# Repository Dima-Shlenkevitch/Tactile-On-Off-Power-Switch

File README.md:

# Tactile ON / OFF Power Switch

## Project Overview
This project focuses on replacing a mechanical switch with a tactile push button and a latch circuit.

The project was inspired by an excellent video from Great Scott:
https://www.youtube.com/watch?v=y1ROEogHF7A

The main circuit remains similar to the reference design.

## Key features of this design include:
* Small footprint
* SMD components
* Mechanical enclosure for panel installation

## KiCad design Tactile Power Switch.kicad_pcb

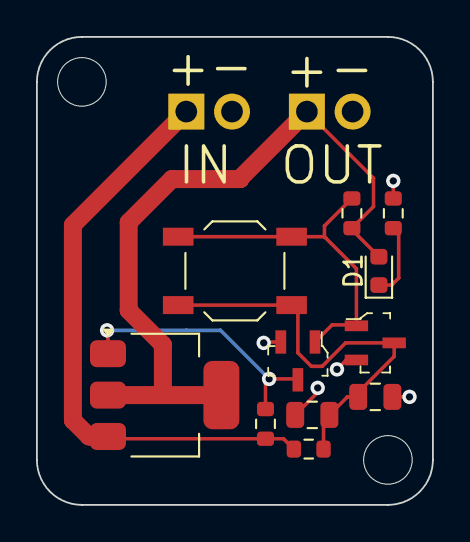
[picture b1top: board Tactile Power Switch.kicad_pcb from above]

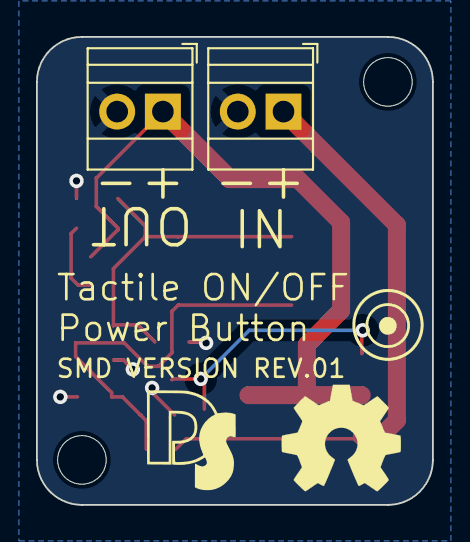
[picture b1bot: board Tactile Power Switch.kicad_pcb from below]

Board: 2 copper layers, 22.0 x 26.0 mm, 15 parts (2 on the bottom side), 7 nets.

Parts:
C1, C2: 22uF; C_0805_2012Metric
D1: GREEN; LED_0603_1608Metric
H1, H2: MountingHole; MountingHole_2.7mm_M2.5_ISO7380
J1, J2: OSTTC020162; TerminalBlock_Xinya_XY308-2.54-2P_1x02_P2.54mm_Horizontal
Q1, Q2: BC847B_215; SOT-23-3
Q4: NDT2955; SOT-223
R1, R2, R3: 100K; R_0603_1608Metric
R4: 1K; R_0603_1608Metric
SW1: SW_SPST; SW_SPST_TL3342

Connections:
+12V: J1.1, Q4.3, R1.1, R3.1
GND: C1.2, C2.2, J1.2, J2.2, Q1.2 (E), Q2.2 (E), R4.2
unnamed: D1.1 (K), R4.1
unnamed: Q1.1 (B), Q2.1 (B), R2.2, SW1.1 (A)
unnamed: Q1.3 (C), Q4.1, R1.2
unnamed: C1.1, C2.1, Q2.3 (C), R3.2, SW1.2 (B)
VDD: D1.2 (A), J2.1, Q4.2, Q4.4, R2.1

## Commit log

2024-09-06 Project init
2024-09-06 Create LICENSE
2024-09-06 Schmatics after final component selection
2024-09-06 Initial component placement
2024-09-11 Placement Finished
2024-09-11 Palcement Change, Screw Terminal footfrint change to 2.54 inch and overall pcb outline optimization
2024-09-11 Initial Layout Finished - Next step to add silkscreen and final check
2024-09-11 Silkscreen logos and description added
2024-09-12 Terminal output connector configureation change
2024-09-12 .gitignore update
2024-09-12 SMD version: Placement is done
2024-09-12 save changes
2024-09-12 Silkscreen added
2024-09-12 MOSFET footprint update, Silkscreen update
2024-09-12 mfg file initiated
2024-09-12 mfg files added
2024-09-12 smd version restored + mfg file created
2024-09-18 CAD model generated
2024-09-18 SMD CAD model generated
2024-10-08 Project Documentation added
